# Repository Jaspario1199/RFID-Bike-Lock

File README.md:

# RFID Bike Lock

**Current DFM print prototype: [VELOX rev3f](releases/rev3f/README.md).** Use its 16 labeled STEP files and [build guide](releases/rev3f/PRINT_BUILD_REV3F.md), with the corrected model frozen at `releases/rev3f/snapshot/cad/cnc_casing_cq.py`. Coupons first; spool deferred; printer profile still pending. The older source/export folders and instructions below are retained as historical lineages and must not be mixed with rev3f.

A frame-mounted, RFID/NFC-unlocked bike lock with a retractable anti-cut steel cable.

The lock is a stainless-steel clamshell cylinder that clamps permanently onto the bike
frame over a compressible liner. A retractable steel cable lives on a spring-loaded spool
in the bottom of the housing; you pull it out, loop it through the wheel or around a rack,
and click the cable head into a latch on top. Tapping an authorized NFC fob (or phone —
see the design doc for the honest caveats) fires a solenoid that pulls the locking pin and
releases the cable, which then reels itself back in.

## Repo map — everything lives on one branch, organized by iteration

| Path | What it is |
|---|---|
| [`DESIGN.md`](DESIGN.md) | The full engineering design document: user workflow, electronics, wiring, power budget, mechanical dimensions, water/power hardening (§4.5), security analysis |
| [`BOM.md`](BOM.md) | Bill of materials — every part, quantity, estimated price (v0.8 all-M3 heat-set fastener standard + v0.8.3 weatherproofing items) |
| [`BUILD.md`](BUILD.md) | The authoritative bench build sequence + print-orientation table (`--dfm`) |
| [`ASSEMBLY.md`](ASSEMBLY.md) | Assembly/DFM audit + v0.8.3 weatherproofing steps (printed v0.8 lineage) |
| [`CAD_METHOD.md`](CAD_METHOD.md) | **Portable method doc** — how to model and verify mechanical parts with an agent: the gate catalogue, the iteration loop, honesty rules, and an opening prompt for a new project |
| [`BENCH_BUILD.md`](BENCH_BUILD.md) | **Start here for the electronics** — seven bench stages using only the delivered parts, with workarounds for the TP4056/AMS1117/cap that haven't arrived |
| [`WIRING.md`](WIRING.md) | **The electrical build in detail** — starts with the [wiring diagram](renders/electrical/wiring_diagram.png) — power domains, full net list, the RC522 3.3 V trap, driver-card layout, build order with expected measurements, failure table |
| [`CAD_AUDIT.md`](CAD_AUDIT.md) | **Build audit of the CNC casing (rev 3e)** — what `--audit` checks beyond the geometry gates (wire/connector envelopes, nuts, plugs, thread engagement, pin insertion, machining numerics), every defect it found and what moved |
| [`ASSEMBLY_CNC.md`](ASSEMBLY_CNC.md) | **The step-by-step build manual for the current CNC casing (rev 3e)** — print settings, every screw, bench checkpoints, stage-by-stage assembly, troubleshooting |
| [`INTERNALS.md`](INTERNALS.md) | **How every electronic mates inside** — per-part contact faces, screws, wiring paths, keyed to `renders/internals/` |
| [`CNC_CASING.md`](CNC_CASING.md) | **The machined-casing redesign** — CNC-first architecture (tube-half chassis + inside-out bolted boxes, bottom hinge pin + one guarded closure screw, centred spool puck, 60° swing gated, electronics stack-up gated, no inserts), DFM rulebook, decisions; model `cad/cnc_casing_cq.py`, STEP `cnc-design/step/`, drawings `cnc-design/drawings/`, renders `renders/cnc/` |
| [`firmware/`](firmware/) | Arduino sketch (v1, ready to flash) + bench bring-up guide |
| [`cad/bike_lock_cq.py`](cad/) | **The single source of truth**: parametric CadQuery model with built-in verification gates (`--gaps`, `--matrix`, `--sweep`, `--support`, `--dfm`) |
| [`newest-design/`](newest-design/) | **LEGACY printed CAD: frozen STEP set (v0.8.3) + MANIFEST** — print/import from here  |
| [`archive/`](archive/) | **Every previous iteration** (v0.2 → v0.7), one folder per version |
| `renders/` | Current assembly renders (closed / open / exploded) |
| `step/`, `stl/` | *Generated build outputs — gitignored; `python cad/bike_lock_cq.py` regenerates them* |

## Iteration index (newest first)

`releases/rev3f/` holds the current DFM print prototype; `newest-design/` holds the older printed lineage; each `archive/vX/` folder holds the frozen **STEP files** for that iteration (per-part
`placed/` set + full assembly + combined multibody) and a `MANIFEST.md` describing exactly
what changed. Older bulk formats (STL, doc snapshots) were trimmed for clarity — git
history preserves every byte.

| Iteration | Where | What it was |
|---|---|---|
| **v0.8.3** (legacy) | [`newest-design/`](newest-design/) | Environmental + DFM hardening: latch-bore & drum weep drains, TPU USB port plug, flush-printing cart, `--dfm` orientation scan, 6 V-rail power option, weatherproofing BOM |
| v0.8.2 | git history of `newest-design/` (MANIFEST §v0.8.2) | Structural audit: `--support` gate, all 17 under-supported heat-set holes fixed, driver card moved onto the pedestal cart (Option C) |
| v0.8 / v0.8.1 | same MANIFEST, §v0.8/§v0.8.1 | All-M3 heat-set fastener rebuild + snug-fit pocket tuning (Ø4.0 locked) + test coupon |
| v0.7 | [`archive/v0.7/`](archive/v0.7/) | Electronics as placed reference bodies; driver relocation; release process begins |
| v0.5–v0.6 | `cad/` git history | Spine+door consumer-install architecture; hinge rod; verification gates born |
| v0.3–v0.4 | [`archive/v0.3/`, `archive/v0.4/`](archive/) | Early CadQuery restructure + slim-top architecture (source + STEP kept) |
| v0.2 | [`archive/v0.2-openscad/`](archive/v0.2-openscad/) | Original OpenSCAD sketch |

## Status

**Design phase — firmware written, nothing physically built yet.** The next milestones
(detailed at the end of `DESIGN.md`) are:

1. Breadboard the electronics (Nano + PN532 + solenoid) and prove the unlock flow —
   the firmware and a step-by-step bring-up guide are waiting in `firmware/`
2. 3D-print the v1 housing (PETG first article; ASA for the outdoor unit) from
   `newest-design/` — print orientations in `BUILD.md` §3b
3. Fabricate the stainless housing

## Key design decisions so far

- **MCU:** Arduino Nano (upgrade path to 3.3 V Pro Mini for longer battery life)
- **Reader:** PN532 NFC module. Keys: NTAG213 sticker on the owner's phone case +
  keychain fobs (owner has an iPhone, which can't act as a hobby NFC key, so no
  companion app is planned)
- **Battery:** 103450 LiPo pouch 2000 mAh (protected) + TP4056 USB-C charge board — the 18650 stopped packaging at v0.4
- **Locking:** insert-to-lock needs **no power** (ramped cable head snaps past a spring pin);
  power is only used for the ~300 ms unlock pulse and brief scan windows
- **One-size-fits-all fit:** a printed TPU *finned* liner (fins bend instead of foam
  crushing, so it stays snug for years) covers Ø32–46 mm down tubes, closure
  detents fine-tune preload, and an included shim sleeve extends down to Ø27 mm skinny
  steel frames — see `DESIGN.md` §6.2
- **Self-guarding closure:** the only screw holding the housing shut sits at the bottom
  of the latch bore, so the locked cable head physically covers it — the case can't be
  unscrewed off the frame while the bike is locked (`DESIGN.md` §6.4). Note: as of the
  v0.6 CAD audit, four *other* service joints (hatch, spine cover, hinge cap, lid) are
  ordinary external screws reachable on the locked bike without unlocking anything —
  see `DESIGN.md` §7 for the honest security consequences and the production mitigation
  plan
- **v1 housing is 3D printed** (ASA for outdoor UV resistance); the latch keeps a steel
  pin + bushing even in plastic
- **Dead-battery behavior:** fail-secure — a dead battery stays locked, and the USB-C
  charge port doubles as the sole emergency input: any phone power bank runs the lock
  instantly for an unlock (`DESIGN.md` §8). There is no cam-lock backstop — it was
  deleted at v0.4 (the slim top never had a wall tall enough for its barrel)

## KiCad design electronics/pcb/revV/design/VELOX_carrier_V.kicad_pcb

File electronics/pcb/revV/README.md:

# VELOX Rev V — FEDC Voltera V-One prototype

This version is a two-sided printed-ink control carrier for the FEDC V-One. Open `design/VELOX_carrier_V.kicad_pro` in KiCad 9. Copper rivets connect the printed layers: small rivets for vias and large rivets for top-mounted Nano sockets and 2.54 mm headers. Bottom-mounted SMD parts are soldered to ink using the qualified Voltera process. There is no chemical through-hole plating, printed solder mask or printed silkscreen. Assembly markings are provided in the views.

The evaluated single-sided route needed16 insulated wire links, so the selected design uses two printed sides for a cleaner harness. The final layout uses25 small interlayer rivets,50 large header/socket rivets and one short insulated link, JP1 from C5.2 to C4.2. All75 rivets are installed parts, not plated holes. `rivet_map.csv` gives the drilled connection coordinates, net and rivet type; count them when estimating assembly effort.

This is an engineering review prototype, not a qualified bike-use product or a claim that FEDC has accepted the job. Digital results are in `validation.json`. Exact stock rivet fit, solder adhesion, ink resistance/current capability, component ratings, external power assembly and physical enclosure installation remain qualification gates.

## Files

- `previews/`: actual schematic, underside ink layout and annotated assembly/wire map.
- `jumpers.csv` / `jumpers.json`: install every wire, between the named existing solder lands. Cut lengths include slack as a starting estimate; route and trim to the real assembly.
- `pin_map.csv`: carrier connector and Nano pin functions.
- `BOM_review.csv`: onboard parts and remaining part-selection inputs.
- `SYSTEM_WIRING.md`: exact external power/driver architecture, panel/reader wiring, sequence and bench checks.
- `manufacturing_REVIEW_ONLY/`: top/bottom Gerbers, separate outline and 0.7/1.6 mm drill files; no copper-layer text or outlines.
- `FEDC_REVIEW_ONLY.zip`: small manufacturing review bundle for technician consultation, not an automatic service submission.
- `mechanical/`: board fit reference and conservative populated-carrier envelope. External power modules are not located by this envelope.

## FEDC process target

FEDC publishes a V-One with 128 × 116 mm area, 0.2 mm minimum trace/spacing, 0.65 mm IC pitch, 0603 passive minimum and drill sizes 0.7/0.8/0.9/1.0/1.6 mm. This layout targets >=0.35 mm signal traces, >=0.30 mm spacing, wider logic-power traces and 0805 passives. No solid ground fills are printed. Main logic-power traces target0.6mm; SMT escape necks and constrained low-current branches may be0.35mm. The coupon and loaded-rail measurements must qualify the actual process. Small interlayer rivets use0.7mm drill /1.3mm land (stock flange0.9mm); large header rivets use the dimensions below. Through-hole lands use 1.6 mm drill / 2.24 mm pad for large rivets with 1.0 mm bore / 2.2 mm head. This modest flange margin and actual header bore fit must be qualified with the stock rivets; 2.54 mm connector pitch limits widening.

Mounting holes are **1.6 mm pilots**, to match the listed drill set. Fixture and hand-finish them to 3.2 mm for M3 after curing; mount centers match Rev B. Both sides reserve a 6.6 mm diameter hardware-clearance envelope. Do not order the copper-clad milling process for this ink design. Verify a blank insulating FR1/FR4 substrate and the actual ink batch/process with the technician. Use nominal 1.6 mm substrate, subject to rivet length and final thickness qualification.

## Electrical scope

The Nano, reader, buttons, LED resistors, buzzer driver and battery divider are on the carrier. The charger, battery fuse/RUN switch, regulators and coil-power driver remain external; see `SYSTEM_WIRING.md`. This reduces vias and avoids putting the coil's high current through silver ink. It may increase external harness volume; enclosure installation needs a prototype check.

The sheet-resistance value in a datasheet is only a starting estimate. Different cure, ink thickness and temperature change actual performance. The supplied test coupon measures the specific process before committing the carrier. There is no solder mask protection on the prototype: insulating standoffs, wire jackets, strain relief and inspection matter.

## Reproduction

Run `build.py`, `route.py`, `schematic_writer.py`, `sync_board.py`, `finish.py`, then regenerate with `schematic_writer.py` and `sync_board.py` before `validate.py` and `publish.py`. `finish.py` applies the reviewed local ADC-return spacing correction and models JP1 explicitly; do not skip it. Generation/routing use pcbnew 7 and numpy; native checks/exports use KiCad CLI 9. Previews use matplotlib/CairoSVG; mechanical envelopes use CadQuery. Do not run build on the final routed board unless regenerating the full sequence.

## Primary references

- https://fedc.engr.tamu.edu/faq/prototyping-center/pcb-faq/
- https://fedc.engr.tamu.edu/facility/prototyping-center/index/
- https://fedc.engr.tamu.edu/services-home/service-request-form/
- https://docs.voltera.io/docs/v-one/learn-v-one/circuit-design-for-v-one/circuit-design-guidelines
- Nano/Pololu/AO3400A interface sources retained in `interfaces.json`.

## Validation result

Native KiCad9.0.9 checks: zero ERC violations, DRC violations, unconnected items or schematic/PCB parity issues. Independent functional checks cover62 connected pins across21 functional nets, including the installed JP1 bridge. No individual DRC exclusions are used. These are digital checks; they do not establish ink conductivity, solder/rivet reliability or a physically installable final lock assembly.

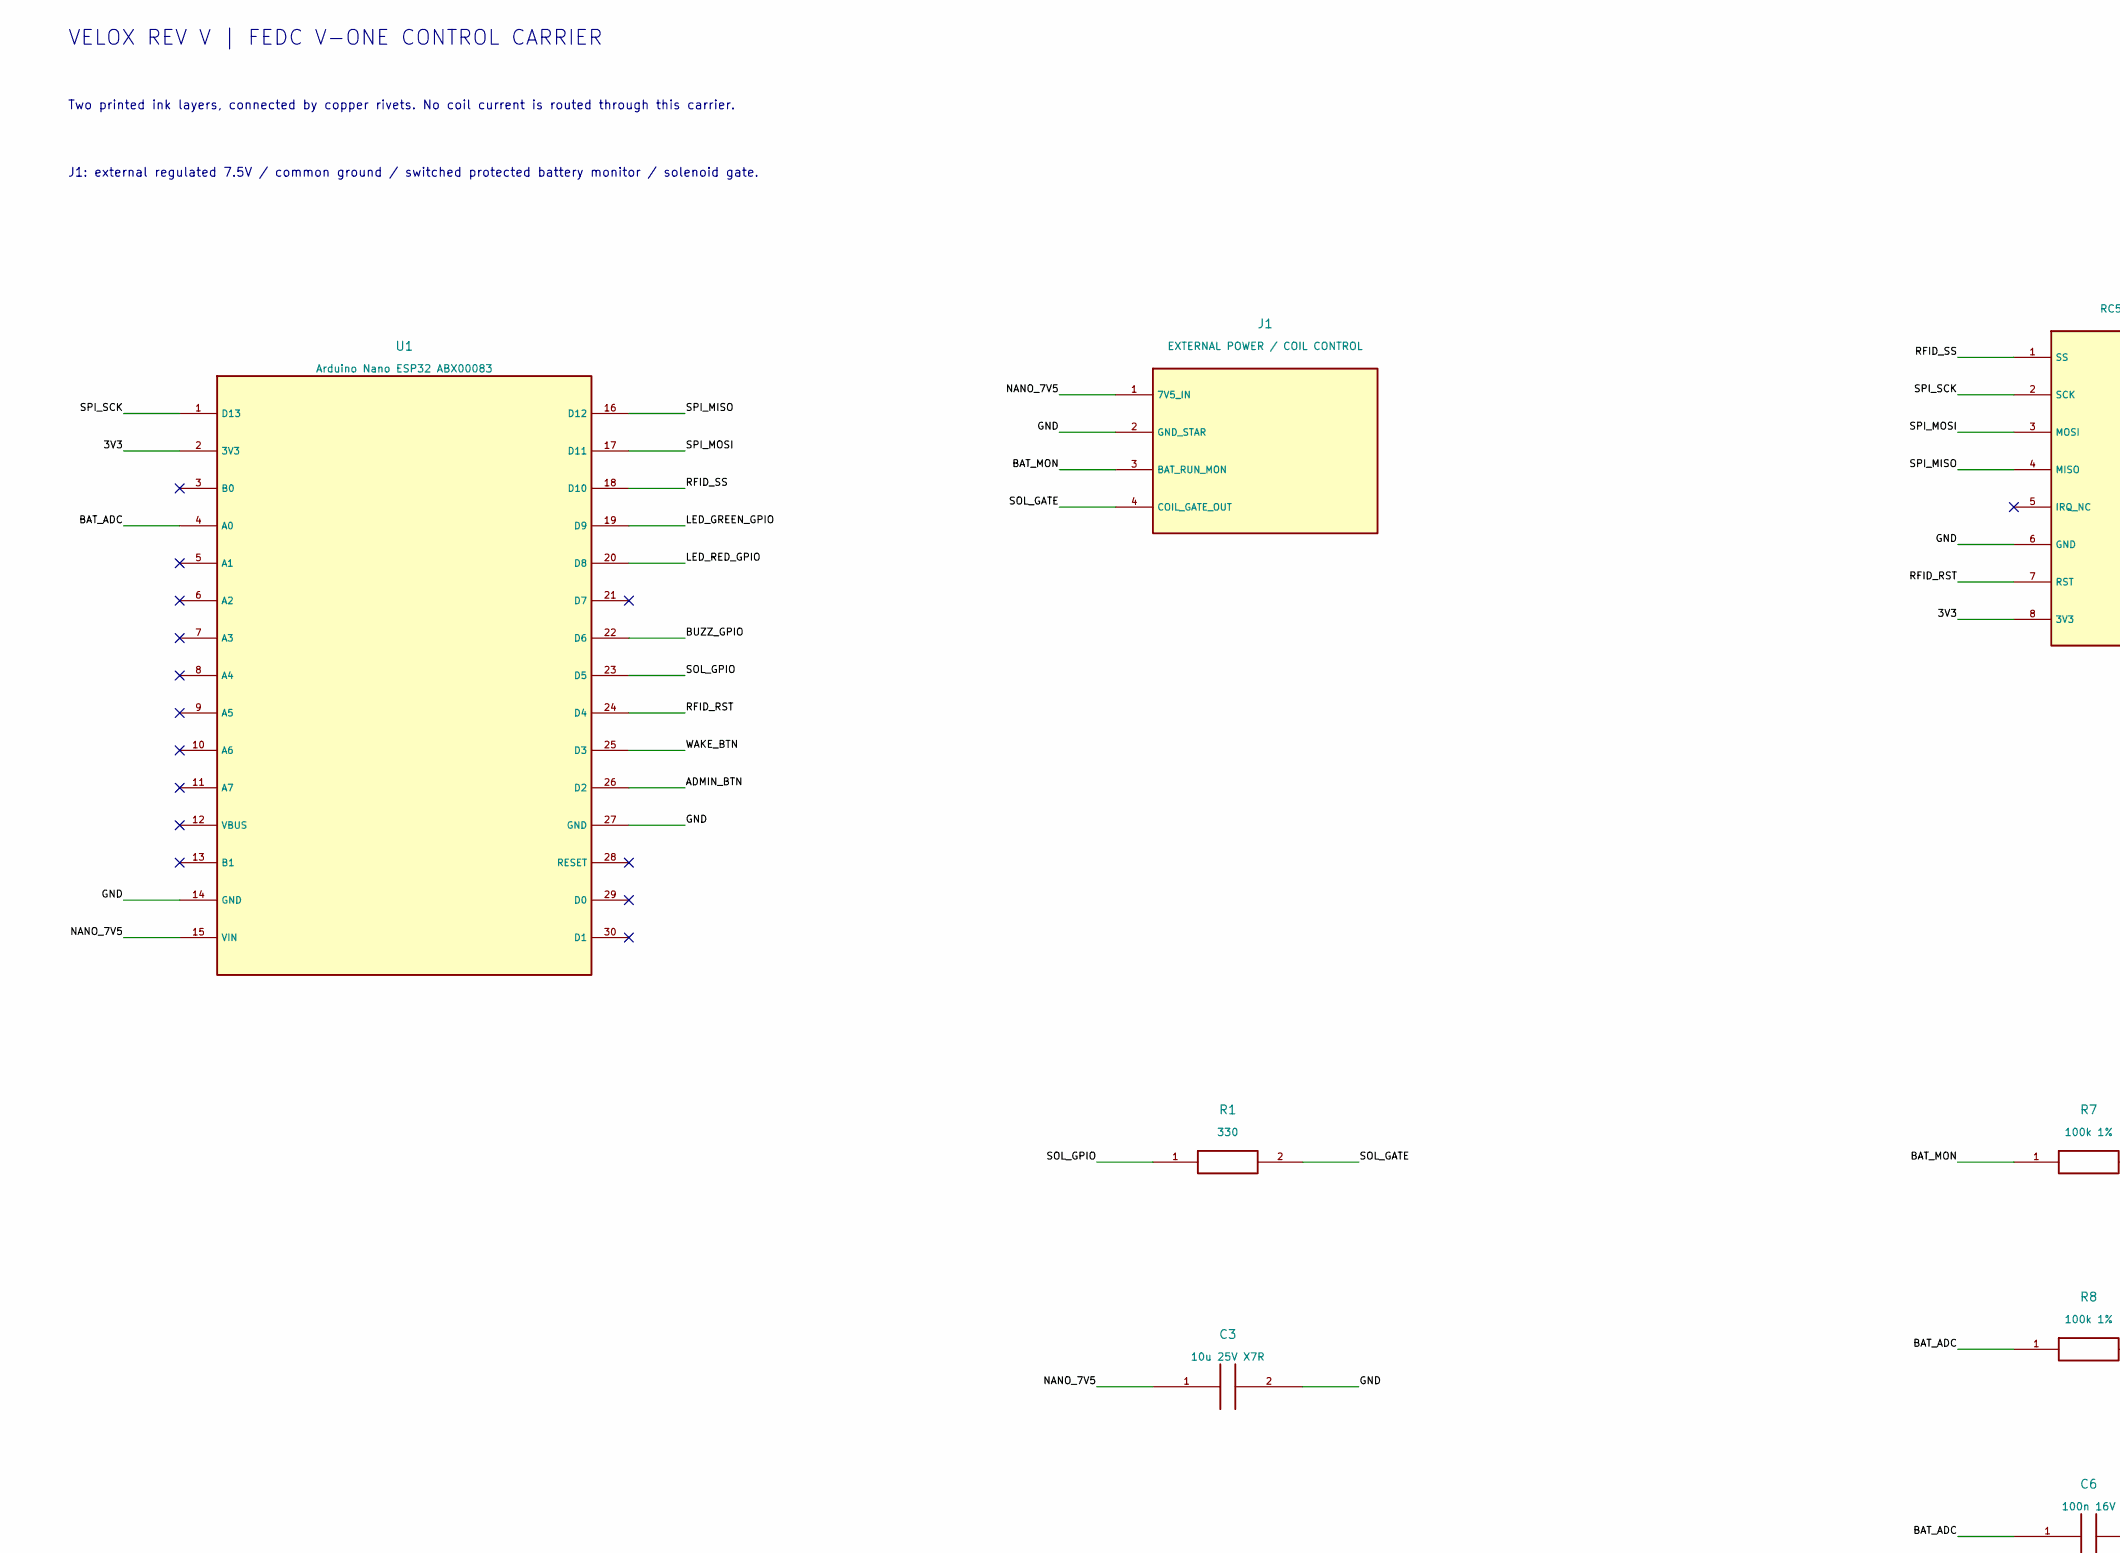
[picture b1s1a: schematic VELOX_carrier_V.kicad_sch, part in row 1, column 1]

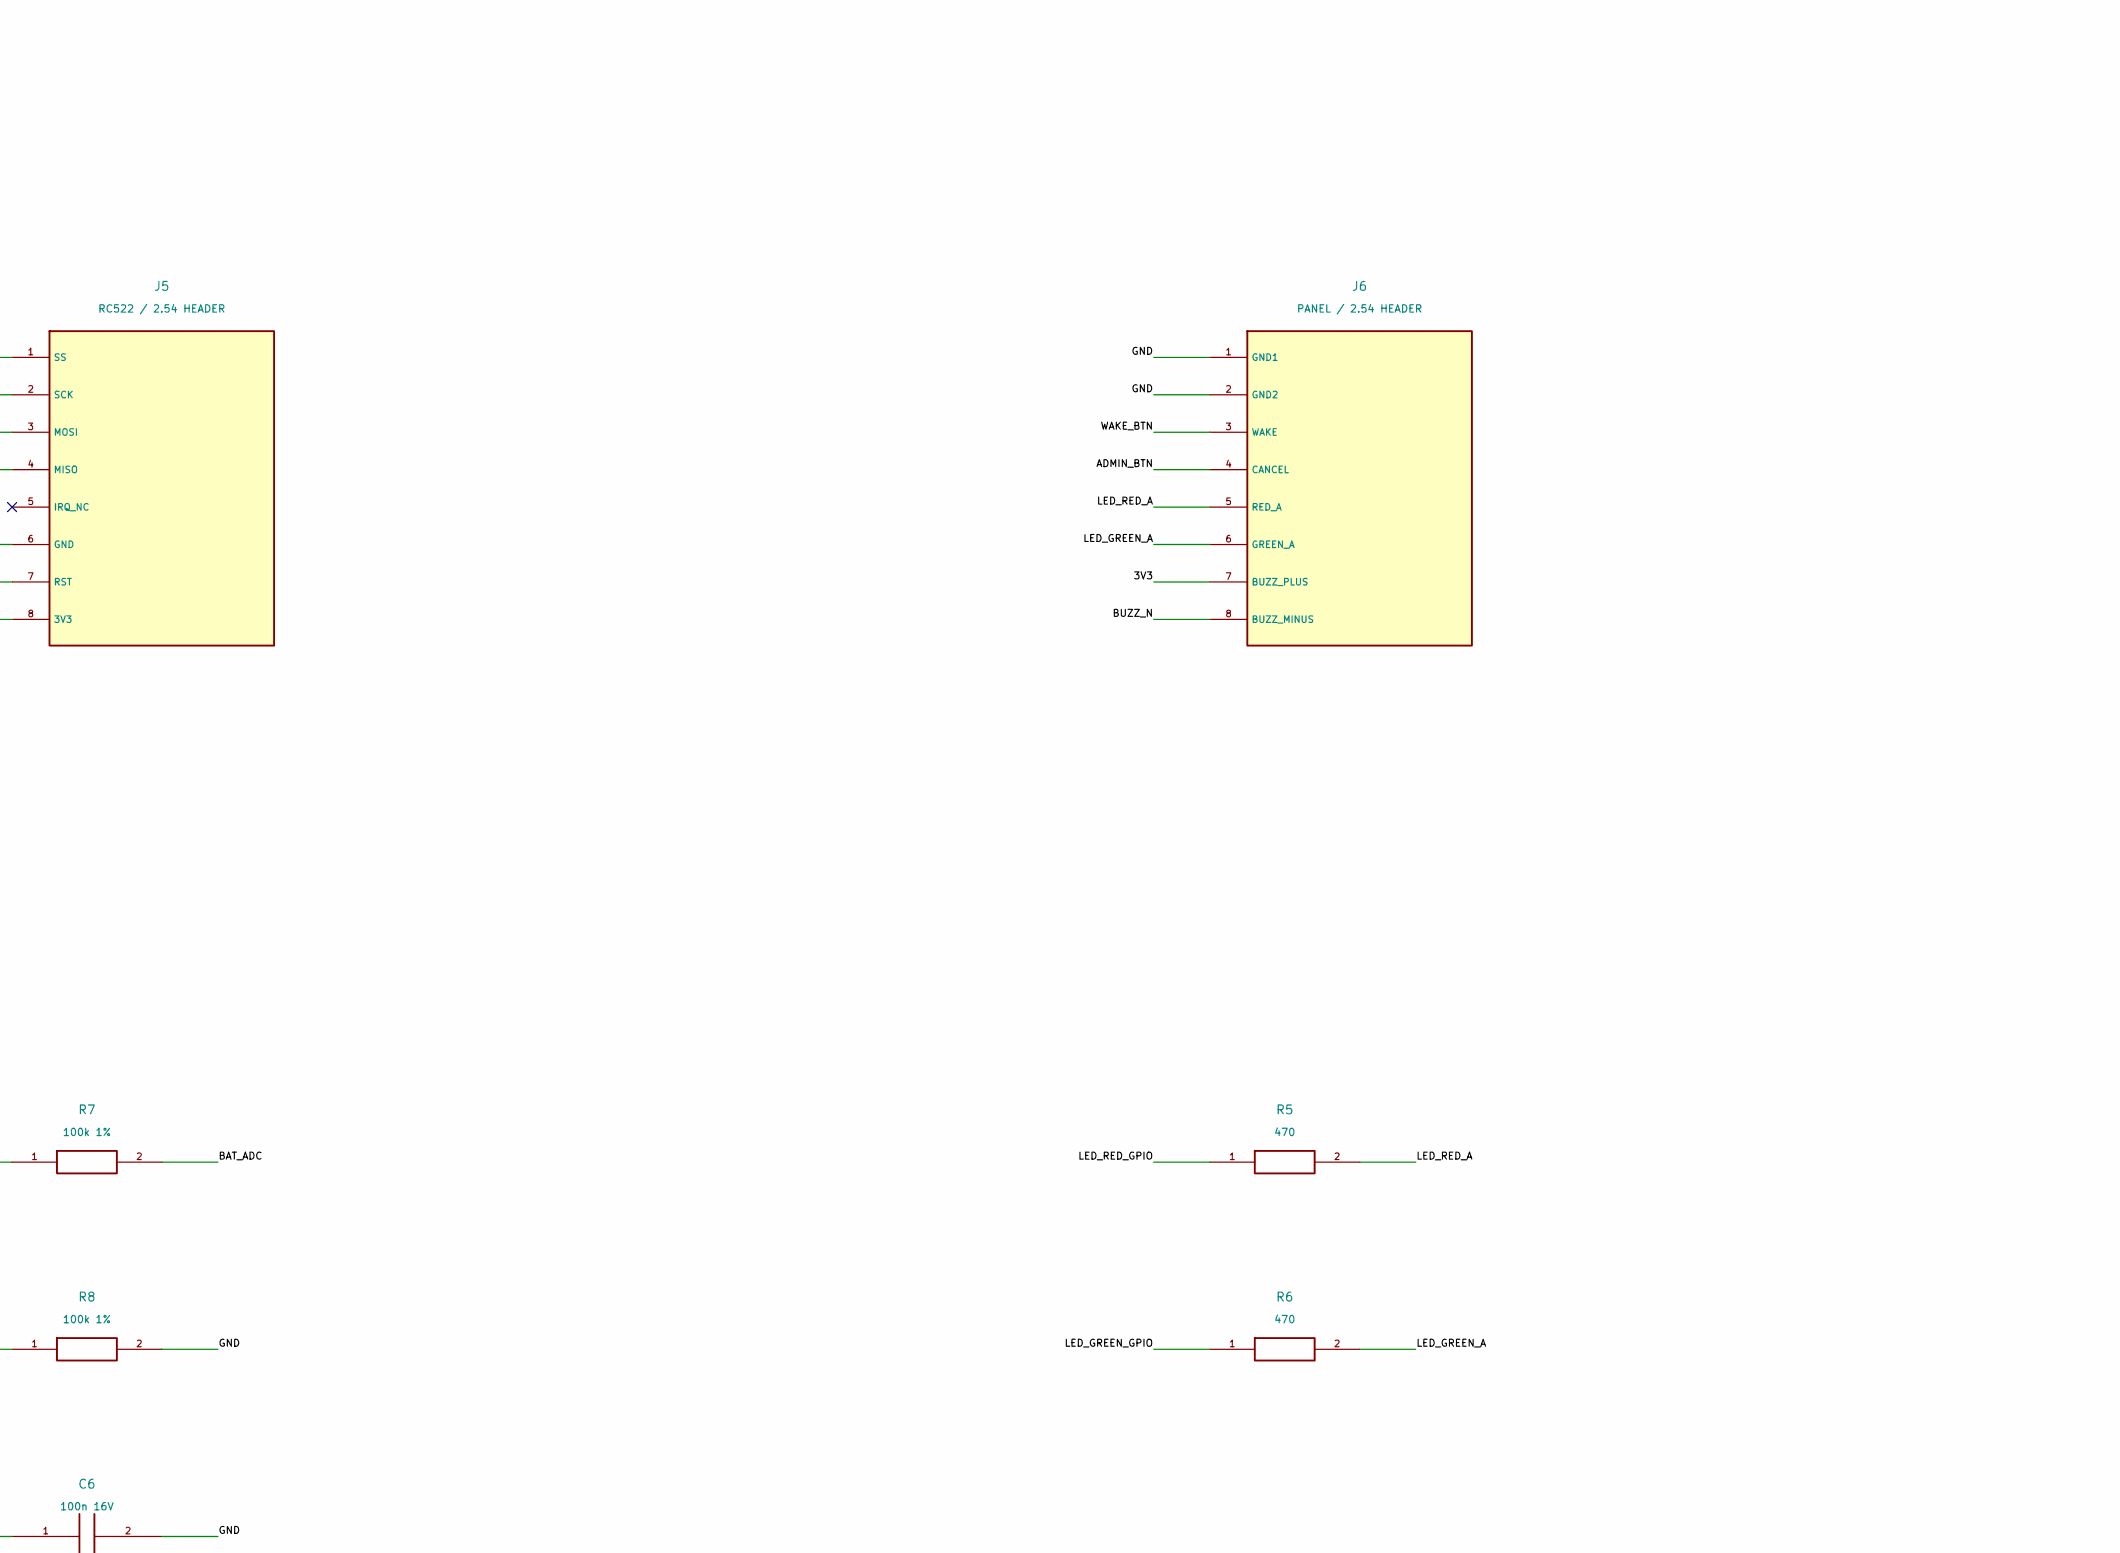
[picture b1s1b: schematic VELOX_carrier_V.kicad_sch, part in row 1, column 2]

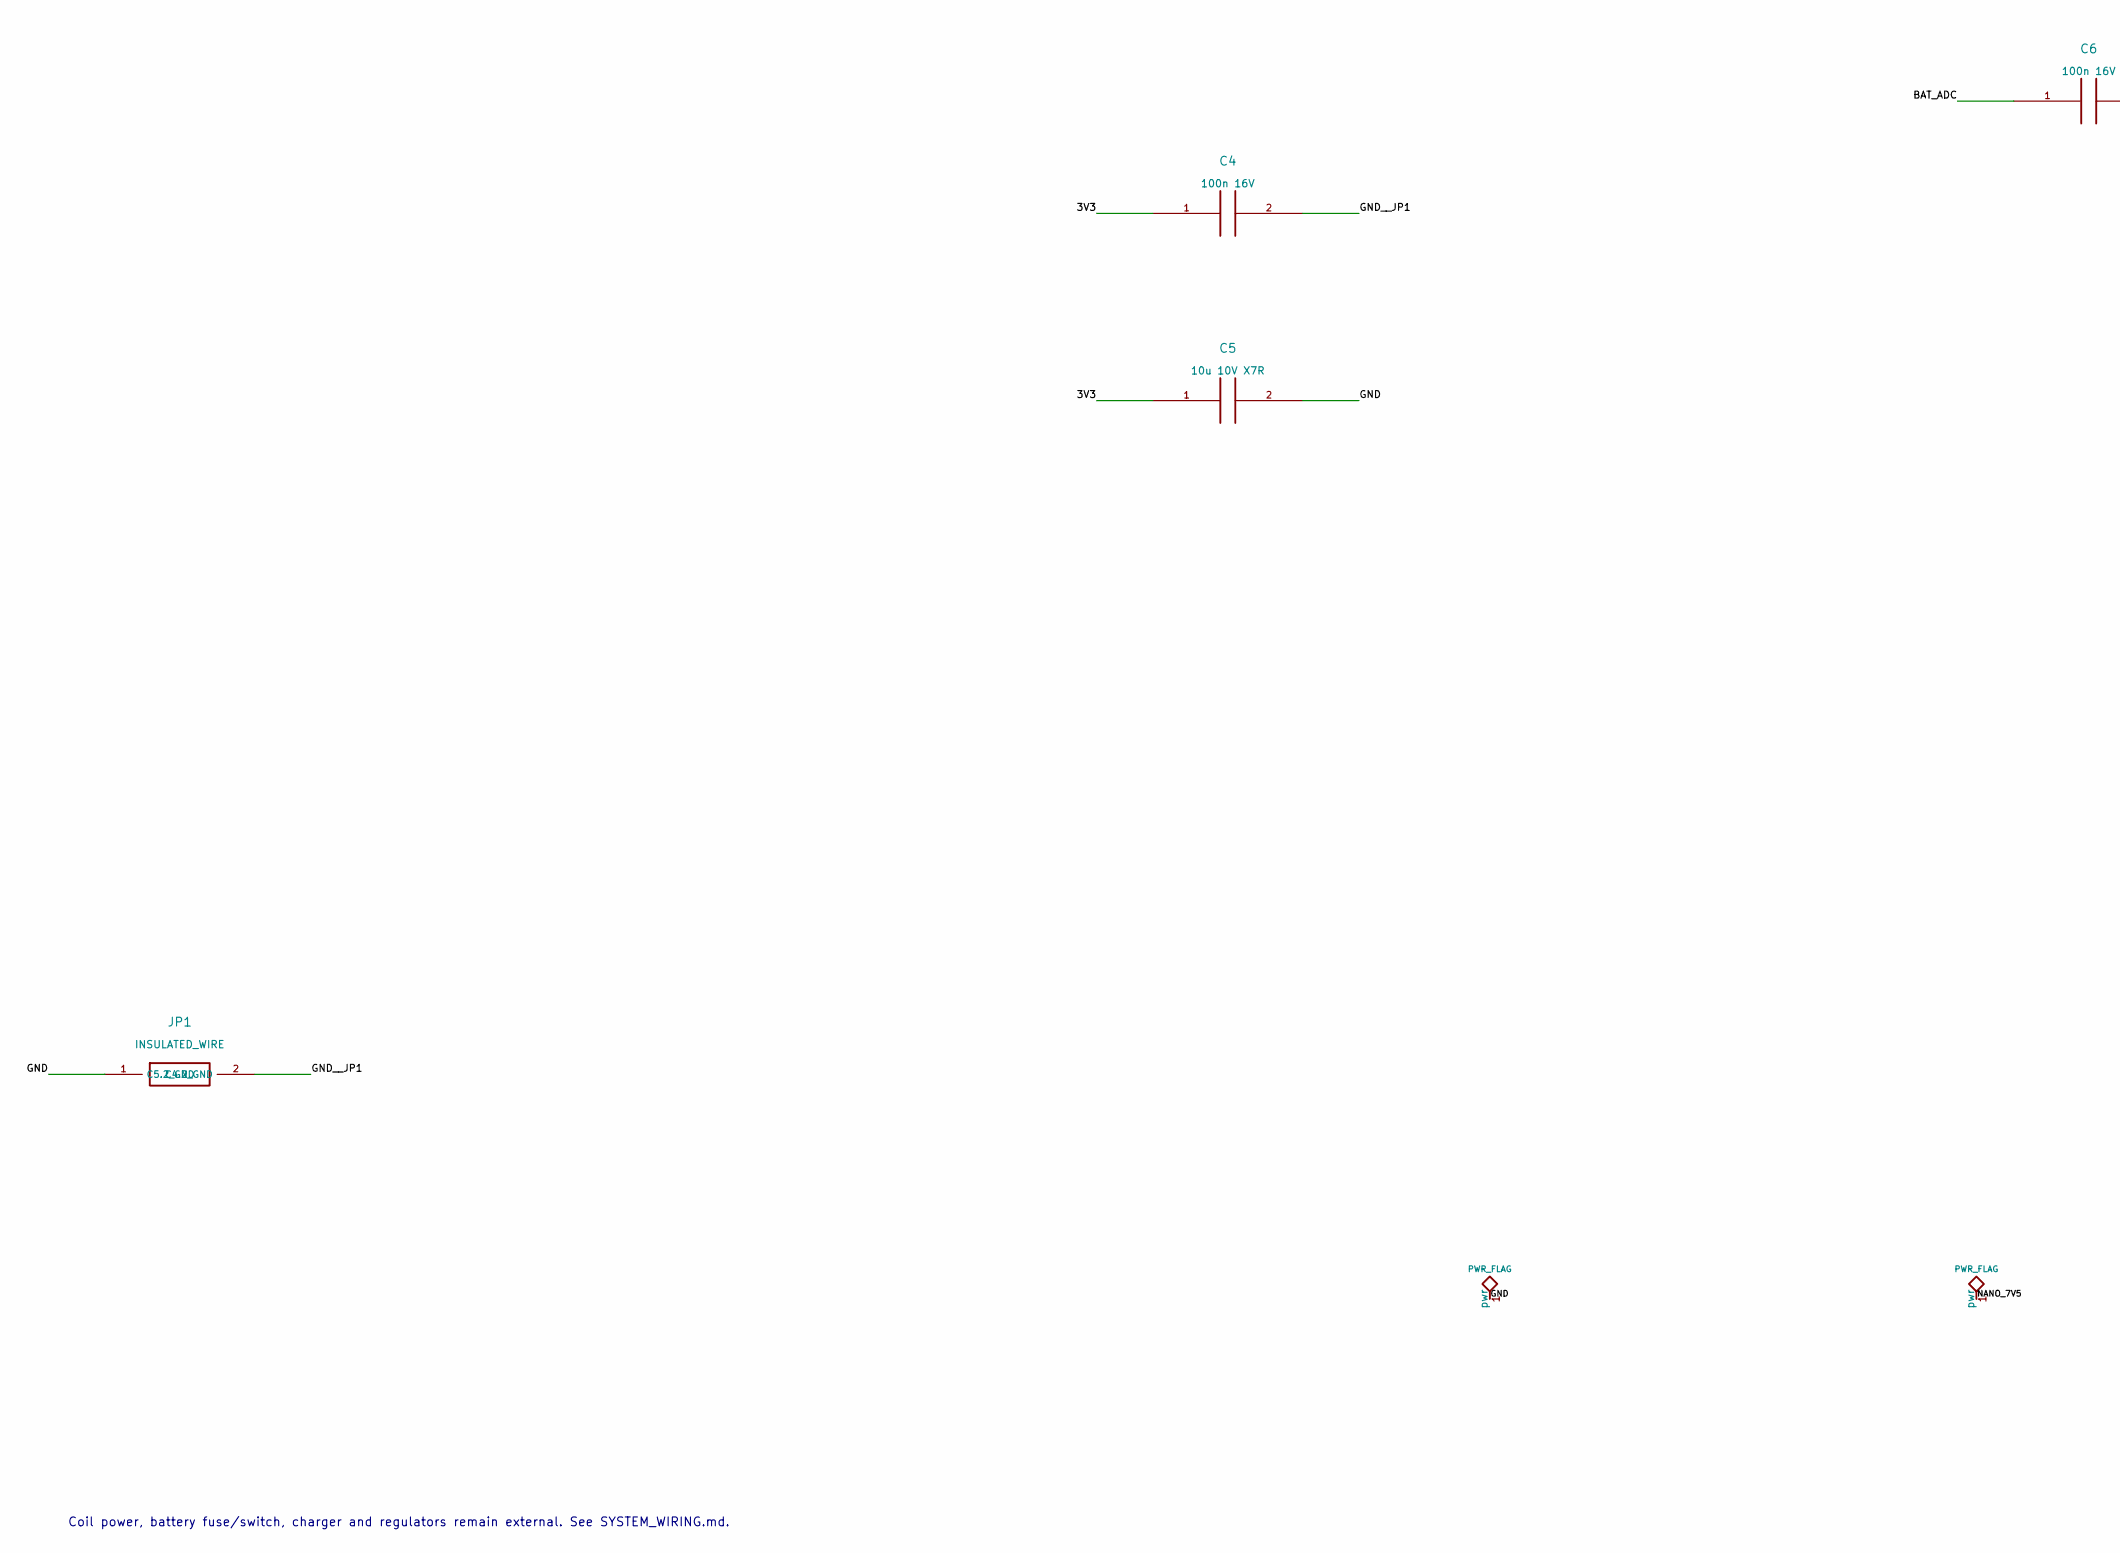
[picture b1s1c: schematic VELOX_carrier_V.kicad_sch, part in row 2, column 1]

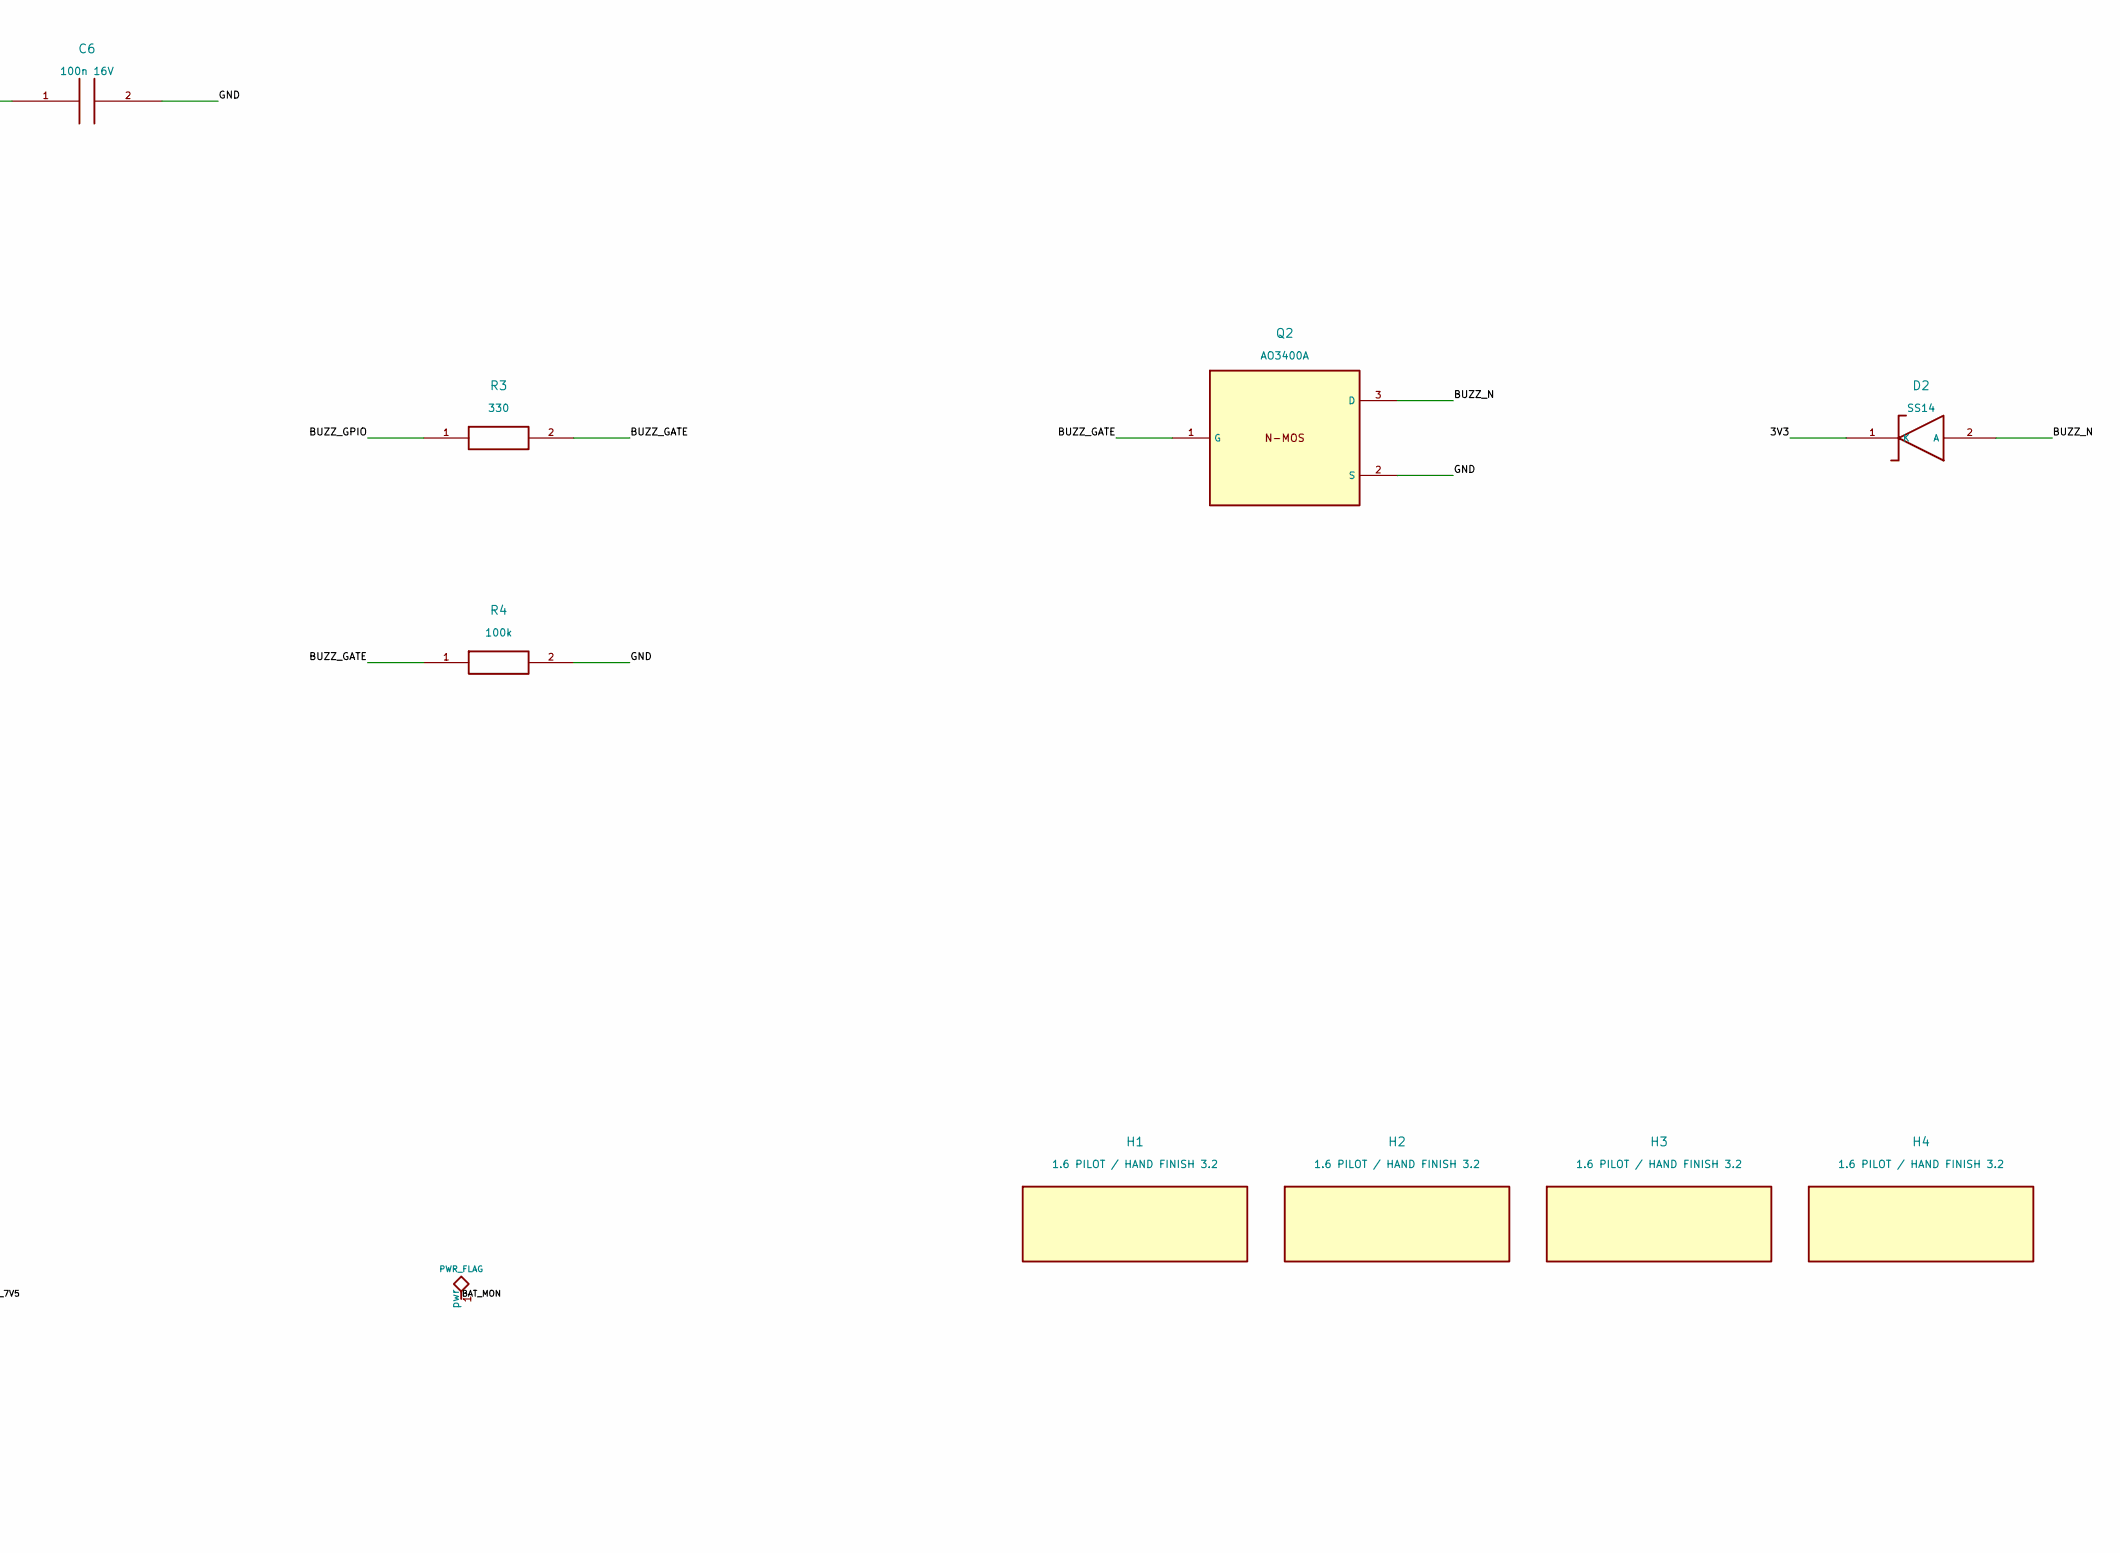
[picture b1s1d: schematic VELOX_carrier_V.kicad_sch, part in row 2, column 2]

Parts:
C3: 10u 25V X7R; C_0805_2012Metric_Pad1.18x1.45mm_HandSolder
C4, C6: 100n 16V; C_0805_2012Metric_Pad1.18x1.45mm_HandSolder
C5: 10u 10V X7R; C_0805_2012Metric_Pad1.18x1.45mm_HandSolder
D2: SS14; D_SMA
H1, H2, H3, H4: 1.6 PILOT / HAND FINISH 3.2; MountingHole_3.2mm_M3
J1: EXTERNAL POWER / COIL CONTROL; Riveted_J1
J5: RC522 / 2.54 HEADER; Riveted_J5
J6: PANEL / 2.54 HEADER; Riveted_J6
JP1: INSULATED_WIRE; Wire_JP1
Q2: AO3400A; SOT-23
R1, R3: 330; R_0805_2012Metric_Pad1.20x1.40mm_HandSolder
R4: 100k; R_0805_2012Metric_Pad1.20x1.40mm_HandSolder
R5, R6: 470; R_0805_2012Metric_Pad1.20x1.40mm_HandSolder
R7, R8: 100k 1%; R_0805_2012Metric_Pad1.20x1.40mm_HandSolder
U1: Arduino Nano ESP32 ABX00083; Nano_ESP32_Riveted_Sockets

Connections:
/3V3: C4.1, C5.1, D2.1 (K), J5.8 (3V3), J6.7 (BUZZ_PLUS), U1.2 (3V3)
/ADMIN_BTN: J6.4 (CANCEL), U1.26 (D2)
/BAT_ADC: C6.1, R7.2, R8.1, U1.4 (A0)
/BAT_MON: J1.3 (BAT_RUN_MON), R7.1
/BUZZ_GATE: Q2.1 (G), R3.2, R4.1
/BUZZ_GPIO: R3.1, U1.22 (D6)
/BUZZ_N: D2.2 (A), J6.8 (BUZZ_MINUS), Q2.3 (D)
/GND: C3.2, C5.2, C6.2, J1.2 (GND_STAR), J5.6 (GND), J6.1 (GND1), J6.2 (GND2), JP1.1 (C5.2_GND), Q2.2 (S), R4.2, R8.2, U1.14 (GND), U1.27 (GND)
/GND__JP1: C4.2, JP1.2 (C4.2_GND)
/LED_GREEN_A: J6.6 (GREEN_A), R6.2
/LED_GREEN_GPIO: R6.1, U1.19 (D9)
/LED_RED_A: J6.5 (RED_A), R5.2
/LED_RED_GPIO: R5.1, U1.20 (D8)
/NANO_7V5: C3.1, J1.1 (7V5_IN), U1.15 (VIN)
/RFID_RST: J5.7 (RST), U1.24 (D4)
/RFID_SS: J5.1 (SS), U1.18 (D10)
/SOL_GATE: J1.4 (COIL_GATE_OUT), R1.2
/SOL_GPIO: R1.1, U1.23 (D5)
/SPI_MISO: J5.4 (MISO), U1.16 (D12)
/SPI_MOSI: J5.3 (MOSI), U1.17 (D11)
/SPI_SCK: J5.2 (SCK), U1.1 (D13)
/WAKE_BTN: J6.3 (WAKE), U1.25 (D3)

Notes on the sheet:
VELOX REV V | FEDC V-ONE CONTROL CARRIER
Two printed ink layers, connected by copper rivets. No coil current is routed through this carrier.
J1: external regulated 7.5V / common ground / switched protected battery monitor / solenoid gate.
Coil power, battery fuse/switch, charger and regulators remain external. See SYSTEM_WIRING.md.

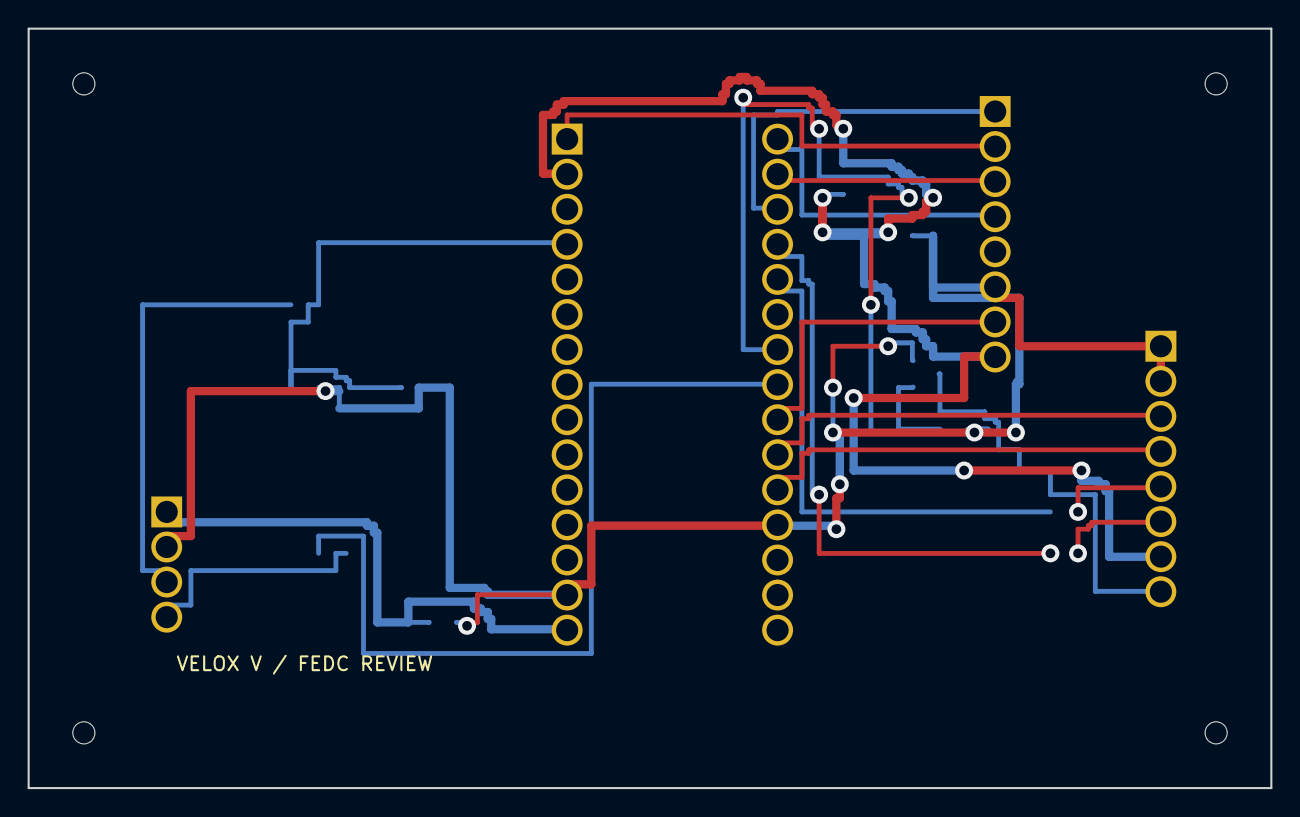
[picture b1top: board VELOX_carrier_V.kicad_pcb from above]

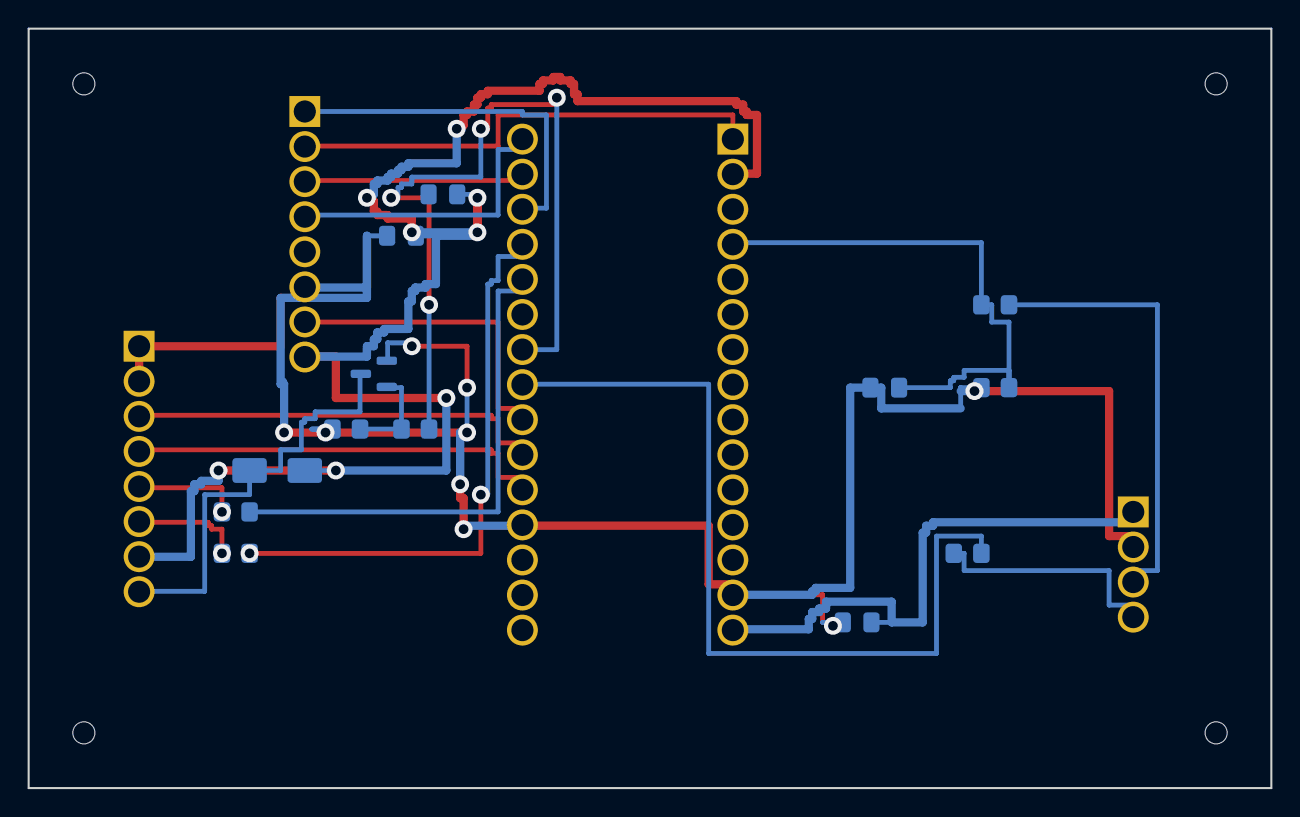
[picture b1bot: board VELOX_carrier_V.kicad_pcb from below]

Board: 2 copper layers, 90.0 x 55.0 mm, 22 parts (13 on the bottom side), 22 nets.

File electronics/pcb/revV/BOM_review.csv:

Reference,Value,Footprint,Qualification
U1,Arduino Nano ESP32 ABX00083,VELOX:Nano_ESP32_Riveted_Sockets,ABX00083 only; socket stack to measure
J1,EXTERNAL POWER / COIL CONTROL,VELOX:Riveted_J1,Exact MPN/rating and solder process to qualify; wire cut lengths and header/socket stack to verify
J5,RC522 / 2.54 HEADER,VELOX:Riveted_J5,Exact MPN/rating and solder process to qualify; wire cut lengths and header/socket stack to verify
J6,PANEL / 2.54 HEADER,VELOX:Riveted_J6,Exact MPN/rating and solder process to qualify; wire cut lengths and header/socket stack to verify
R1,330,VELOX:R_0805_2012Metric_Pad1.20x1.40mm_HandSolder,Exact MPN/rating and solder process to qualify; wire cut lengths and header/socket stack to verify
R7,100k 1%,VELOX:R_0805_2012Metric_Pad1.20x1.40mm_HandSolder,Exact MPN/rating and solder process to qualify; wire cut lengths and header/socket stack to verify
R8,100k 1%,VELOX:R_0805_2012Metric_Pad1.20x1.40mm_HandSolder,Exact MPN/rating and solder process to qualify; wire cut lengths and header/socket stack to verify
C6,100n 16V,VELOX:C_0805_2012Metric_Pad1.18x1.45mm_HandSolder,Exact MPN/rating and solder process to qualify; wire cut lengths and header/socket stack to verify
C3,10u 25V X7R,VELOX:C_0805_2012Metric_Pad1.18x1.45mm_HandSolder,Exact MPN/rating and solder process to qualify; wire cut lengths and header/socket stack to verify
C4,100n 16V,VELOX:C_0805_2012Metric_Pad1.18x1.45mm_HandSolder,Exact MPN/rating and solder process to qualify; wire cut lengths and header/socket stack to verify
C5,10u 10V X7R,VELOX:C_0805_2012Metric_Pad1.18x1.45mm_HandSolder,Exact MPN/rating and solder process to qualify; wire cut lengths and header/socket stack to verify
R5,470,VELOX:R_0805_2012Metric_Pad1.20x1.40mm_HandSolder,Exact MPN/rating and solder process to qualify; wire cut lengths and header/socket stack to verify
R6,470,VELOX:R_0805_2012Metric_Pad1.20x1.40mm_HandSolder,Exact MPN/rating and solder process to qualify; wire cut lengths and header/socket stack to verify
Q2,AO3400A,VELOX:SOT-23,Exact MPN/rating and solder process to qualify; wire cut lengths and header/socket stack to verify
R3,330,VELOX:R_0805_2012Metric_Pad1.20x1.40mm_HandSolder,Exact MPN/rating and solder process to qualify; wire cut lengths and header/socket stack to verify
R4,100k,VELOX:R_0805_2012Metric_Pad1.20x1.40mm_HandSolder,Exact MPN/rating and solder process to qualify; wire cut lengths and header/socket stack to verify
D2,SS14,VELOX:D_SMA,Exact MPN/rating and solder process to qualify; wire cut lengths and header/socket stack to verify
JP1,INSULATED_WIRE,VELOX:Wire_JP1,Exact MPN/rating and solder process to qualify; wire cut lengths and header/socket stack to verify
